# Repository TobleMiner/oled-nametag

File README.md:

OLED Nametag
============

This repository contains the design file for a fully open source
electronic name badge with monochrome OLED display.  

**I would not recommend ordering RevA yet as there are a number of
issues with that version. See
[Rev A issues](https://github.com/TobleMiner/oled-nametag#rev-a-issues)
for details.**

# Features

 - Bright, sunlight readable OLED display
 - Infinity constrast ratio
 - Support for GIF animations
 - WLAN AP support
 - Web interface for management of animations
 - Automatic brightness adjustment
 - 8h+ runtime

# Construction

All fabrication files are located in `fab`.  

## PCB

The main PCB have been optimized for manufacturing through JLCPCB.  
Most components can also be assmbled by JLCPCB directly.  

## Display

The display used can be one of:
 - UG-5664ALBEF01
 - UG-5664ASWEF01
 - ER-OLED032-1 (all variants)

Other menchanically compatible SSD1322-based parts can also be used.

## Housing

The device housing is 3D printable and designed to suit most 3D printing
processes, especially SLA and FDM. Good results have also been achieved with
MJF and SLS printing.  

There are three different fabrication files for the case top part,
depending on the thickness of the lithium batteries used.  

Additionally 4 button actuators need to be printed for each OLED badge.
Those are also contained in the OpenSCAD design files and fabrication
output.

# Assembly

## PCB

When choosing PCB assembly through JLCPCB only two PCB components need to
be assmbled manually:
 - WLAN antenna (AE1)
 - Ambient light sensor (U4)

## Display

The display is mounted to the top side of the PCB using double sided
adhesive tape with a thickness of .15mm. Align to top of the PCB (side
with USB-C port) with the top of the display.

## Batteries

The device needs two 303030, 403030 or 503030 cells as a power source.  
The batteries need to be mounted on the bottom side of the PCB. Double-
sided adhesive foam tape with a thickness of 2mm is recommended for this
purpose.

## Housing

Place the button actuators into the housing first, then slide in the PCB
with both display and batteries attached and stuck down.  

At this point the badge should look like this:  

Finally screw on the top lid iwht six 4mm M1 fine thread self tapping
screws.

# Firmware

The OLED badge is running fully Open Source firmware. For the purpose of
enabling WLAN connectivity vendor-provided binary blobs are required.  
The firmware source can be found here:  
[https://github.com/TobleMiner/oled-nametag-firmware](https://github.com/TobleMiner/oled-nametag-firmware)

# Rev A issues

Rev A is very much a prototype. It has the following known issues:
 - USB D- and D+ are swapped on the ESP32-S3, needs bodge to swap data lines
 - OLED SPI mode is inconvenient and incompatible with current firmware, connect R1 to GND
 - R21 is too large, preventing soft power down, replace with 1k

The current state of the repository does not reflect Rev A but a
potential Rev B. Please note that this state of the design has not been
tested yet.

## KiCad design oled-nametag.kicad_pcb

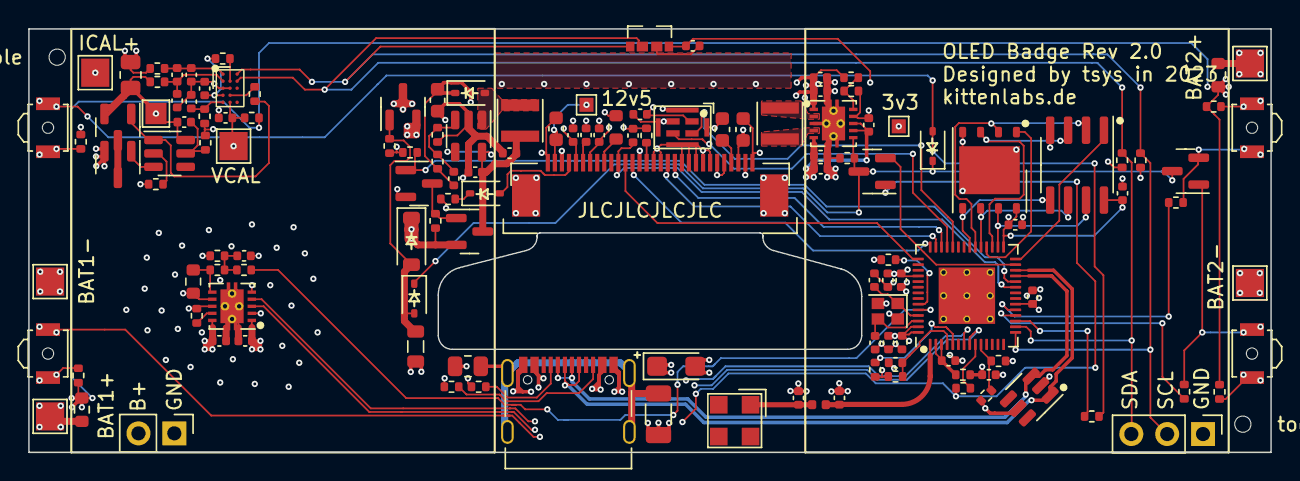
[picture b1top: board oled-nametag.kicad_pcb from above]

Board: 4 copper layers, 88.0 x 30.0 mm, 138 parts (0 on the bottom side), 88 nets.

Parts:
AE1: Antenna_Shield; 2065130001
C1, C7, C10, C15, C23, C29, C40: 1uF; C_0402_1005Metric
C2, C9, C14, C16, C17, C21, C22, C25, C27, C34, C35, C36, C37, C38, C39, C44: 100nF; C_0402_1005Metric
C3, C6, C8, C43: 10uF 25V; C_0603_1608Metric
C4, C5, C13, C18, C26, C28, C30, C31, C32: 10uF; C_0402_1005Metric
C11, C12: 10pF; C_0402_1005Metric
C19, C20, C42: DNP; C_0402_1005Metric
C24: 1nF; C_1206_3216Metric
C33: 10uF; CP_EIA-3216-10_Kemet-I
C41: 22pF; C_0402_1005Metric
D1, D2: 1N5819WS; D_SOD-323
D3: B5819W; D_SOD-123
D4, D6: BAV70; SOT-23
D5: 1N4148WS; D_SOD-323
D7: 4148WS; D_SOD-323
F2, F3: 2A; R_0603_1608Metric
FB1: Bead; L_0805_2012Metric
H1, H2: ToolingHole; ToolingHole_JLCSMT
J1: USB_C_Receptacle_USB2.0; USB_C_Receptacle_Palconn_UTC16-G
J2: I2C; PinHeader_1x03_P2.54mm_Vertical
J3: LOAD; PinHeader_1x02_P2.54mm_Vertical
L1: 10uH; L_Taiyo-Yuden_MD-3030
L2: 0R; L_0402_1005Metric
L3: 2.2uH; L_Taiyo-Yuden_MD-3030
Q1, Q2: AO3401A; SOT-23
Q4, Q5: AO3400A; SOT-23
Q6: 2N7002; SOT-23
R1, R22, R23, R24, R25, R27, R32, R39, R40, R41: 100R; R_0402_1005Metric
R2: 680k; R_0603_1608Metric
R3: 50R; R_0402_1005Metric
R4, R6, R10, R11: 47k; R_0402_1005Metric
R5, R8, R9, R16, R19, R20, R28, R31: 5.1k; R_0402_1005Metric
R7, R34: 0R; R_0402_1005Metric
R12, R21: 1k; R_0402_1005Metric
R13: 470R; R_0402_1005Metric
R14: 2.7k; R_0603_1608Metric
R15, R17, R29, R30, R33, R42, R43, R44: 10k; R_0402_1005Metric
R18: 200k; R_0805_2012Metric
R26: 10mR; R_0805_2012Metric
R35, R36, R37, R38: DNP; R_0402_1005Metric
SW1: Power; SW_SPST_B3U-3000P-B
SW2: BTN1; SW_SPST_B3U-3000P-B
SW3: BTN2; SW_SPST_B3U-3000P-B
SW4: BTN3; SW_SPST_B3U-3000P-B
TP1: ICAL-; TestPoint_Pad_1.5x1.5mm
TP2, TP4: BAT+; TestPoint_Pad_2.0x2.0mm
TP3, TP5: BAT-; TestPoint_Pad_2.0x2.0mm
TP6: ICAL+; TestPoint_Pad_2.0x2.0mm
TP7: +12v5; TestPoint_Pad_1.0x1.0mm
TP8: +3v3; TestPoint_Pad_1.0x1.0mm
TP10: VCAL; TestPoint_Pad_2.0x2.0mm
U1: FFC_30P_TC_P0.5mm_0.5K-AS-30PWB
U2: W25Q128; WSON-8-1EP_6x5mm_P1.27mm_EP3.4x4.3mm
U3: ESP32-S3; QFN-56-1EP_7x7mm_P0.4mm_EP4x4mm_ThermalVias_0.3mm
U4: VEML3235SL
U5: ST_HCLGA-4LD_3x4mm
U6: TPS61040DBV; SOT-23-5
U7: FM2113; SOT-23-6
U8: BQ24081; Texas_DRC0010J_ThermalVias.3
U9: SRV05-4; SOT-23-6
U10: BQ27546; DSBGA-15_BQ27546_I2C_1.95x2.6mm_P0.5mm
U11: TPS63001; Texas_DRC0010J_ThermalVias.3
U12: ESP-PSRAM32; SOIC-8_3.9x4.9mm_P1.27mm
Y1: 40MHz; Crystal_SMD_2016-4Pin_2.0x1.6mm

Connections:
+3V3: C1.1, C2.1, C13.2, C15.1, C16.2, C17.2, C18.2, C21.2, C22.2, C26.2, C30.2, C31.2, R6.1, R7.2, R8.1, R9.1, R31.1, R34.1, TP8.1, U1.24 (VDDIO), U1.26 (VCI), U3.20 (VDD3P3_RTC), U3.46 (VDD3P3_CPU), U3.55 (VDDA), U3.56 (VDDA), U4.1 (VDD), U5.1 (VDD), U11.1 (VOUT)
+BATT: C27.2, F2.2, F3.2, J3.2, Q1.3 (D), R13.1, R22.1, R23.1, R27.1, R39.1, R40.1, R41.1, U8.10 (OUT)
/ESP32/CHRG_PWM: R38.2, U3.52 (GPIO46)
/ESP32/D+: J1.A6 (D+), J1.B6 (D+), U3.26 (GPIO20), U9.1 (IO1)
/ESP32/D-: J1.A7 (D-), J1.B7 (D-), U3.25 (GPIO19), U9.3 (IO2)
/ESP32/OLED_CLK: U1.13 (D0/CLK), U3.41 (GPIO36)
/ESP32/OLED_CS: U1.19 (~CS), U3.43 (GPIO38)
/ESP32/OLED_DATA: U1.12 (D1/SIN), U3.40 (GPIO35)
/ESP32/OLED_DC: U1.18 (D/~C), U3.42 (GPIO37)
/ESP32/OLED_EN: Q6.1 (G), R10.1, U3.24 (GPIO18)
/ESP32/OLED_RST: C39.2, U1.20 (~RES), U3.23 (GPIO17)
/ESP32/PDM_CLK: U3.39 (GPIO34), U5.3 (CLK)
/ESP32/PDM_DATA: U3.38 (GPIO33), U5.4 (DATA)
/ESP32/PWR_EN: D4.2 (A), U3.27 (GPIO21)
/ESP32/PWR_ON: D4.1 (A), R29.2, SW1.2
/ESP32/SCL: J2.2, R8.2, U3.15 (GPIO10), U4.4 (SCL), U10.A3 (SCL)
/ESP32/SDA: J2.3, R9.2, U3.16 (GPIO11), U4.3 (SDA), U10.B3 (SDA)
/ESP32/USB_DET: R28.1, R30.1, U3.10 (GPIO5)
/ESP32/VDD_SPI: C10.1, C40.1, U2.8 (VCC), U3.29 (VDD_SPI), U12.8 (VCC)
/ESP32/~BTN1: D7.2 (A), R43.2, SW2.2
/ESP32/~BTN2: D6.1 (A1), R44.2, SW3.1
/ESP32/~BTN3: D6.2 (A2), R42.2, SW4.2
/ESP32/~CHRG: U3.8 (GPIO3), U8.3 (STAT1)
/ESP32/~RST: C9.1, R6.2, U3.4 (CHIP_PU)
/ESP32/~STAT2: U3.7 (GPIO2), U8.4 (STAT2)
/Power/DSG: R32.2, U10.D2 (CE)
/Power/PWR_ON: D4.3 (K), D5.1 (K), D6.3 (K), D7.1 (K), R17.1, U11.6 (EN)
GND: C1.2, C2.2, C3.2, C4.1, C5.1, C6.1, C7.2, C8.2, C9.2, C10.2, C11.2, C12.1, C13.1, C14.2, C15.2, C16.1, C17.1, C18.1, C19.1, C20.1, C21.1, C22.1, C23.2, C24.1, C26.1, C27.1, C28.1, C30.1, C31.1, C32.1, C33.2, C39.1, C40.2, C42.1, C43.2, C44.1, J1.A1 (GND), J1.A12 (GND), J1.B1 (GND), J1.B12 (GND), J2.1, J3.1, Q5.2 (S), Q6.2 (S), R1.1, R2.2, R3.1, R5.1, R10.2, R12.1, R14.1, R15.2, R16.2, R17.2, R18.1, R19.2, R20.1, R21.2, R30.2, R35.2, R37.2, U1.1 (SHIELD), U1.2 (VSS), U1.5 (VLSS), U1.6 (D7), U1.7 (D6), U1.8 (D5), U1.9 (D4), U1.10 (D3), U1.11 (D2), U1.14 (E/~RD), U1.15 (R/~W), U1.17 (BS1), U1.28 (VLSS), U1.30 (SHIELD), U1.ML (MP), U1.MR (MP), U2.4 (GND), U2.9 (EP), U3.57 (GND), U4.2 (GND), U5.2 (L/R), U5.5 (GND), U6.2 (GND), U8.2 (GND), U8.5 (GND), U8.7 (GND), U8.8 (~TE), U8.11 (GND), U9.2 (VN), U11.3 (PGND), U11.9 (GND), U11.11 (PGND), U12.4 (VSS), Y1.2, Y1.4
GND1: C29.1, C34.2, C35.2, C37.1, C38.2, R25.1, R26.1, TP3.1, TP5.1, TP6.1, U10.C1 (VSS), U10.C2 (VSS)
unnamed: AE1.1 (A), C19.2, L2.2
unnamed: C42.2, R36.1, R37.1, R38.1
unnamed: D1.2 (A), U1.27 (VSL)
unnamed: D1.1 (K), R3.2
unnamed: D2.2 (A), L1.2, U6.1 (SW)
unnamed: D3.2 (A), D5.2 (A), FB1.1, Q1.1 (G), R21.1
unnamed: C28.2, C32.2, C44.2, D3.1 (K), Q1.2 (S), Q2.2 (S), R11.2, U11.5 (VIN), U11.7 (PS/SYNC), U11.8 (VINA)
unnamed: F2.1, TP2.1
unnamed: F3.1, TP4.1
unnamed: J1.A5 (CC1), R19.1
unnamed: J1.B5 (CC2), R20.2
unnamed: C24.2, J1.S1 (SHIELD), R18.2
unnamed: C4.2, C5.2, L1.1, Q2.3 (D), U6.4 (EN), U6.5 (VIN)
unnamed: Q2.1 (G), Q6.3 (D), R11.1
unnamed: Q4.3 (D), Q5.3 (D)
unnamed: Q4.1 (G), R32.1, U7.1 (DO)
unnamed: C25.1, Q4.2 (S), R24.1, R26.2, TP1.1, U7.6 (VSS)
unnamed: Q5.1 (G), U7.3 (CO)
unnamed: R27.2, SW1.1
unnamed: R39.2, SW2.1
unnamed: R40.2, SW3.2
unnamed: R41.2, SW4.1
unnamed: R1.2, U1.16 (BS0)
unnamed: R2.1, U1.22 (IREF)
unnamed: C6.2, U1.4 (VCOMH)
unnamed: C7.1, U1.25 (VDD)
unnamed: U2.1 (~CS), U3.32 (SPICS0)
unnamed: R31.2, U3.5 (GPIO0)
unnamed: R29.1, U3.9 (GPIO4)
unnamed: R43.1, U3.17 (GPIO12)
unnamed: R44.1, U3.18 (GPIO13)
unnamed: R42.1, U3.19 (GPIO14)
unnamed: R16.1, U3.51 (GPIO45)
unnamed: C20.2, L2.1, U3.1 (LNA_IN)
unnamed: C11.1, U3.53 (XTAL_N), Y1.1
unnamed: C12.2, U3.54 (XTAL_P), Y1.3
unnamed: C41.1, R4.2, R5.2, U6.3 (FB)
unnamed: C25.2, R13.2, U7.5 (VDD)
unnamed: R12.2, U7.2 (VM)
unnamed: R14.2, R36.2, U8.6 (ISET)
unnamed: R15.1, U8.9 (TS)
unnamed: C35.1, R23.2, TP10.1, U10.E2 (BAT)
unnamed: C34.1, R22.2, U10.E1 (REGIN)
unnamed: C36.2, C38.1, R24.2, U10.B1 (SRN)
unnamed: C36.1, C37.2, R25.2, U10.A1 (SRP)
unnamed: R33.1, U10.B2 (TS)
unnamed: C29.2, R33.2, U10.D1 (VCC)
unnamed: R34.2, R35.1, U11.10 (FB)
unnamed: L3.1, U11.4 (L1)
unnamed: L3.2, U11.2 (L2)
unnamed: U2.6 (CLK), U3.33 (SPICLK), U12.6 (SCLK)
unnamed: U2.3 (IO2), U3.31 (SPIWP), U12.3 (SIO2)
unnamed: U2.7 (IO3), U3.30 (SPIHD), U12.7 (SIO3)
unnamed: U2.5 (DI(IO0)), U3.35 (SPID), U12.5 (SI/SIO)
unnamed: U2.2 (DO(IO1)), U3.34 (SPIQ), U12.2 (SO/SIO)
unnamed: U3.28 (SPICS1), U12.1 (~CE)
VBUS: C23.1, C33.1, FB1.2, J1.A4 (VBUS), J1.A9 (VBUS), J1.B4 (VBUS), J1.B9 (VBUS), R28.2, U8.1 (IN), U9.5 (VP)
VCC: C3.1, C8.1, C41.2, C43.1, D2.1 (K), R4.1, TP7.1, U1.3 (VCC), U1.29 (VCC)
VDD3P3: C14.1, R7.1, U3.2 (VDD3P3), U3.3 (VDD3P3)

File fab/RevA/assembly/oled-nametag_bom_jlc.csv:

"Comment","Designator","Footprint","LCSC Part #"
"10uF","C4,C5,C28,C30,C31,C32,C13,C18,C26","C_0402_1005Metric","C15525"
"10uF 25V","C8,C3,C6","C_0603_1608Metric","C96446"
"10pF","C11,C12","C_0402_1005Metric","C32949"
"1uF","C23,C29,C1,C7,C10,C15,C40","C_0402_1005Metric","C52923"
"1nF","C24","C_1206_3216Metric","C35216"
"100nF","C25,C27,C34,C35,C36,C37,C38,C2,C39,C9,C14,C16,C17,C21,C22","C_0402_1005Metric","C1525"
"10uF","C33","CP_EIA-3216-10_Kemet-I","C7171"
"1N5819WS","D2,D1","D_SOD-323","C191023"
"B5819W","D3","D_SOD-123","C8598"
"BAV70","D4","SOT-23","C68978"
"1N4148WS","D5","D_SOD-323","C2128"
"2A","F2,F3","R_0603_1608Metric","C96542"
"Bead","FB1","L_0805_2012Metric","C1015"
"USB_C_Receptacle_USB2.0","J1","USB_C_Receptacle_Palconn_UTC16-G","C167321"
"10uH","L1","L_1210_3225Metric","C703786"
"0R","L2","L_0402_1005Metric","C17168"
"2.2uH","L3","L_Taiyo-Yuden_MD-3030","C43389"
"AO3401A","Q1,Q2","SOT-23","C15127"
"FS8205A","Q3","SOT-23-6","C2830320"
"2N7002","Q6","SOT-23","C8545"
"680k","R2","R_0603_1608Metric","C25822"
"50R","R3","R_0402_1005Metric","C25120"
"47k","R4,R10,R11,R21,R6","R_0402_1005Metric","C25792"
"0R","R7","R_0402_1005Metric","C17168"
"1k","R12,R14","R_0402_1005Metric","C11702"
"470R","R13","R_0402_1005Metric","C25117"
"10k","R15,R17,R30,R33,R29","R_0402_1005Metric","C25744"
"200k","R18","R_0805_2012Metric","C17539"
"5.1k","R19,R20,R5,R28,R8,R9,R16,R31","R_0402_1005Metric","C25905"
"10mR","R26","R_0805_2012Metric","C5185583"
"100R","R27,R22,R23,R24,R25,R32,R1","R_0402_1005Metric","C25076"
"Power","SW1","SW_SPST_B3U-3000P-B","C963349"
"BTN1","SW2","SW_SPST_B3U-3000P-B","C963349"
"BTN2","SW3","SW_SPST_B3U-3000P-B","C963349"
"BTN3","SW4","SW_SPST_B3U-3000P-B","C963349"
"~","U1","FFC_30P_TC_P0.5mm_0.5K-AS-30PWB","C2911772"
"W25Q128","U2","WSON-8-1EP_6x5mm_P1.27mm_EP3.4x4.3mm","C2689660"
"ESP32-S3","U3","QFN-56-1EP_7x7mm_P0.4mm_EP4x4mm_ThermalVias","C2913192"
"~","U5","ST_HCLGA-4LD_3x4mm","C966942"
"TPS61040DBV","U6","SOT-23-5","C7722"
"DW01+G","U7","SOT-23-6","C14213"
"BQ24081","U8","Texas_DRC0010J_ThermalVias","C555156"
"SRV05-4","U9","SOT-23-6","C85364"
"BQ27546","U10","DSBGA-15_BQ27546_I2C_1.95x2.6mm_P0.5mm","C528629"
"TPS63001","U11","Texas_DRC0010J_ThermalVias","C28060"
"40MHz","Y1","Crystal_SMD_2016-4Pin_2.0x1.6mm","C255898"

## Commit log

2023-04-23 Finish ESP32 fanout
2023-04-23 Add power planes
2023-04-24 Finish first layout revision
2023-04-24 Make EDRC happy (mostly)
2023-04-24 Add 3D models
2023-04-24 Make DRC happy (for the most part)
2023-04-24 Add fuel gauge thermistor
2023-04-24 Add power rail testpoints
2023-04-24 Add PSRAM
    Doom?
2023-04-24 Fix fuel gauge thermistor ground reference
2023-04-24 Add pin 1 and polarity indicators
2023-04-24 Add missing LCSC partnumbers
2023-04-24 Add silkscreen markings
2023-04-24 Adjust to new JLC manufacturing requirements
    Change default minimum via hole size to .3mm
    Replace package thermal vias by .3mm via
2023-04-28 Hide U11 designator
2023-04-30 Hide U8 designator
2023-05-01 Hide U3 designator
2023-05-07 Start rev1.1
    Fixed bugs:
    - Swapped D+ and D-
    - Insufficient pull-down strength on VBUS
    - Default OLED to 4-wire SPI
    - Swap VBUS detect divider from 2/3 to 1/3
2023-05-08 More Rev 1.1 fixes
    - Revert USB_DET voltage divider swap
    - Fix battery gauge temperature sensor reference level
2023-05-09 Reduce charge current to 300mA, Add battery voltage calibration testpoint
2023-05-16 Add initial case design
2023-05-16 case: make model parameterizeable
2023-05-16 case: support configuring board depth and oversize
2023-05-17 case: make board height and screw hole size configureable
2023-05-29 case: make battery thickness configureable
2023-05-29 Add current calibration output
2023-06-13 Add second light sensor position for reversed device mounting
2023-06-13 Add experimental case with reverse mounting option
2023-07-02 Add a readme
2023-07-02 Add license
2023-07-02 Add RevA fabrication files
2023-07-23 Do rough component placement
2023-07-30 Add smaller BAV70 symbol
2023-07-30 Finsh first layout iteration
2023-07-30 Hide silkscreen designators
2023-07-30 Unify text orientation
2023-07-30 Add thermal groundplane to charger
2023-07-30 Add VEML3235SL 3D model
2023-07-30 Replace microphone by one from another manufacturer
    Previous ones were often DOA.
2023-07-30 Improve thermal via stitching on charger IC
2023-07-30 Disable thermal reliefs on charger GND vias
